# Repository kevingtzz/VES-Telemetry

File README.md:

## VES-Telemetry 🚀
Telemetry system for electro-solar vehicle VES-KRATOS
## Hardware 🔧
API frames reception and emission for Zigbee mesh topology architecture implemented on Xbee.
CAN protocol data extraction, processing and emission (Low level).
## Software ⚙️
Multi platform aplication on Electron JS for GPS geolocation and electro-solar vehicle data monitoring on real time.
## Initialization:
* Install dependencies with npm install.
* Install RethinkDB, if you have macOS with homebrew just type on your terminal "brew update && brew install rethinkdb".
* Create the database, go to localhost:8080 and create a database with this name "KRATOS-VES".

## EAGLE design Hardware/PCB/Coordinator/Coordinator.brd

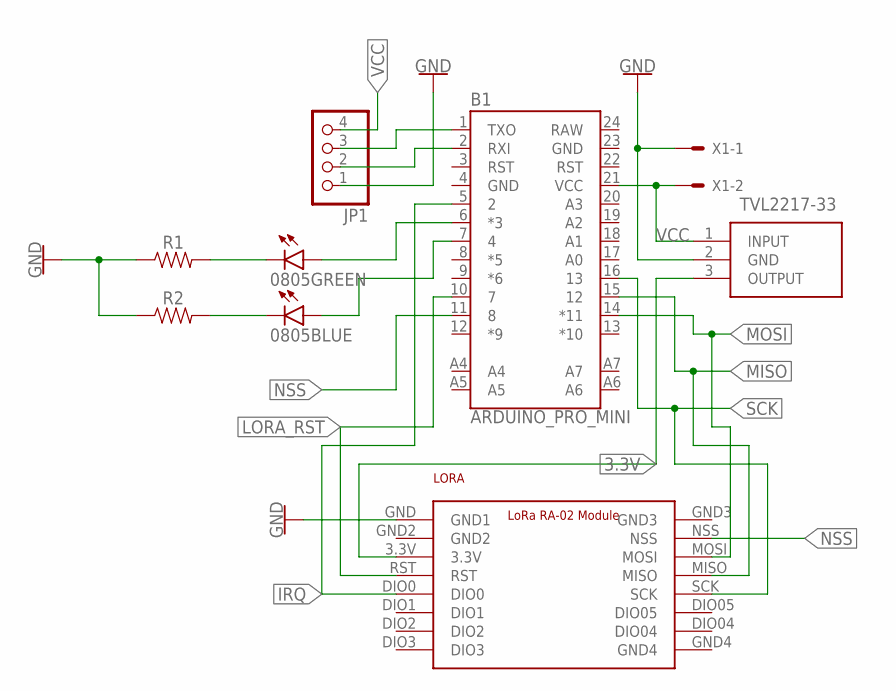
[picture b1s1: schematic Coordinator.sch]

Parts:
0805BLUE, 0805GREEN: LEDCHIPLED_0805; CHIPLED_0805
B1: ARDUINO_PRO_MINI
JP1: PINHD-1X4; 1X04
LORA: LORA_RA-02_MODULE; LORA_RA-02_MODULE_FOOTPRINT
R1, R2: 0805
TVL2217-33: TLV2217-33KCSE3; TO254P470X1016X1965-3P
X1: JST-XH-02-PIN-LONG-PAD; JST-XH-02-PACKAGE-LONG-PAD

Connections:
3.3V: LORA.3.3V, TVL2217-33.3 (OUTPUT)
GND: B1.4 (GND), B1.23 (GND), JP1.1, LORA.GND (GND1), R1.1, R2.1, TVL2217-33.2 (GND), X1.1
IRQ: B1.5 (2), LORA.DIO0
LORA_RST: B1.10 (7), LORA.RST
MISO: B1.15 (12), LORA.MISO
MOSI: B1.14 (*11), LORA.MOSI
unnamed: B1.2 (RXI), JP1.2
unnamed: B1.1 (TXO), JP1.3
unnamed: 0805GREEN.A, B1.6 (*3)
unnamed: 0805BLUE.A, B1.7 (4)
unnamed: 0805GREEN.C, R1.2
unnamed: 0805BLUE.C, R2.2
NSS: B1.11 (8), LORA.NSS
RAW: B1.24 (RAW)
SCK: B1.16 (13), LORA.SCK
VCC: B1.21 (VCC), JP1.4, TVL2217-33.1 (INPUT), X1.2

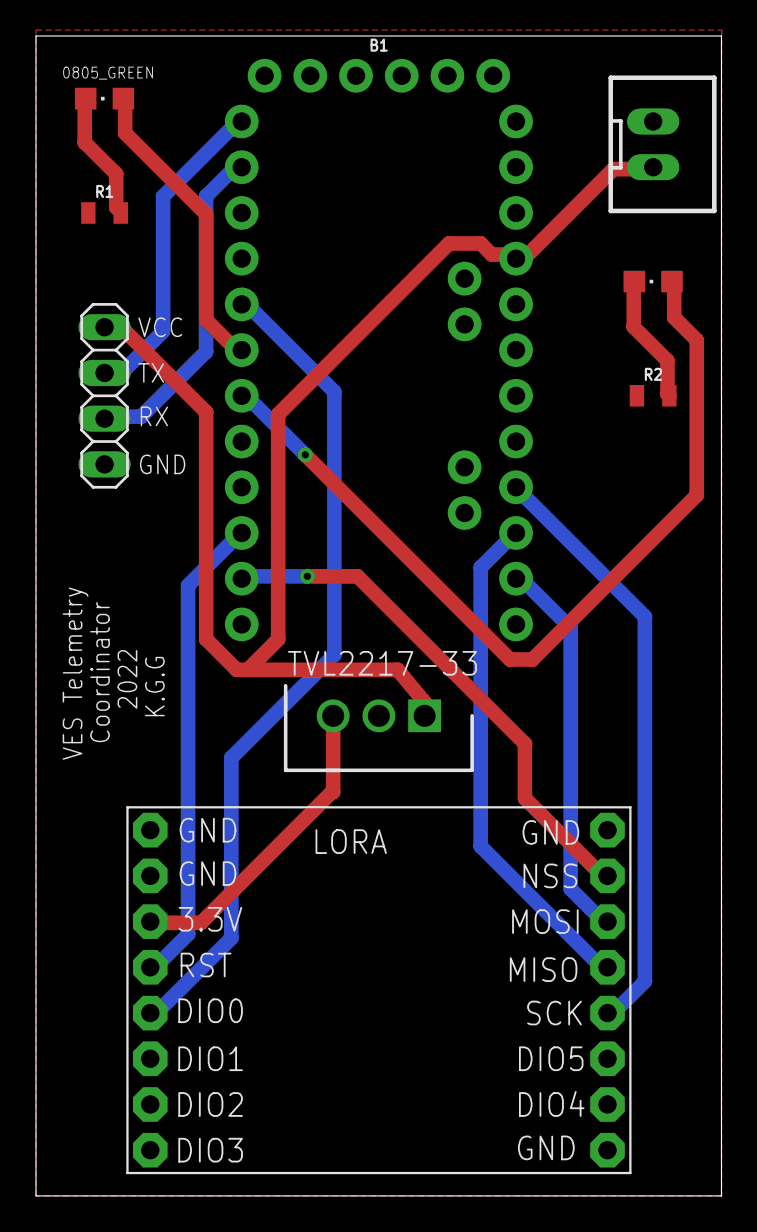
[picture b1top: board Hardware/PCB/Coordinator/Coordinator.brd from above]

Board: 2 copper layers, 38.1 x 64.4 mm, 9 parts (0 on the bottom side), 15 nets.

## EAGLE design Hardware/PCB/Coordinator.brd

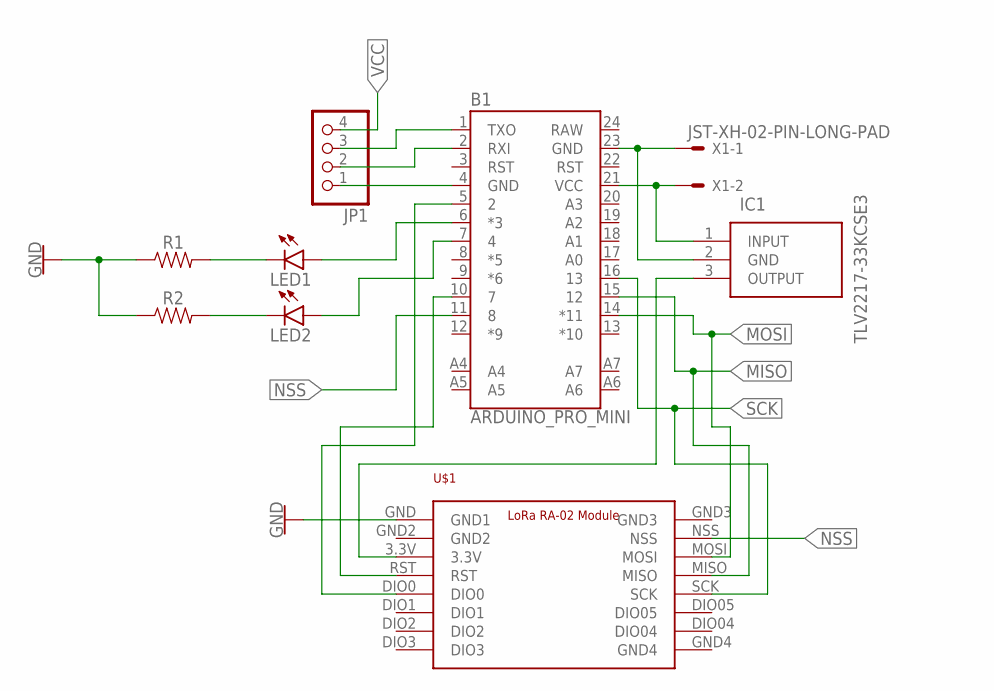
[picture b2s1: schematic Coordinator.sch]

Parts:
B1: ARDUINO_PRO_MINI
IC1: TLV2217-33KCSE3; TO254P470X1016X1965-3P
JP1: PINHD-1X4; 1X04
LED1, LED2: LEDCHIPLED_0805; CHIPLED_0805
R1, R2: 0805
U$1: LORA_RA-02_MODULE; LORA_RA-02_MODULE_FOOTPRINT
X1: JST-XH-02-PIN-LONG-PAD; JST-XH-02-PACKAGE-LONG-PAD

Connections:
GND: R1.1, R2.1, U$1.GND (GND1)
MISO: B1.15 (12), U$1.MISO
MOSI: B1.14 (*11), U$1.MOSI
unnamed: B1.23 (GND), IC1.2 (GND), X1.1
unnamed: B1.21 (VCC), IC1.1 (INPUT), X1.2
unnamed: IC1.3 (OUTPUT), U$1.3.3V
unnamed: B1.4 (GND), JP1.1
unnamed: B1.2 (RXI), JP1.2
unnamed: B1.1 (TXO), JP1.3
unnamed: B1.5 (2), U$1.DIO0
unnamed: B1.10 (7), U$1.RST
unnamed: B1.6 (*3), LED1.A
unnamed: B1.7 (4), LED2.A
unnamed: LED1.C, R1.2
unnamed: LED2.C, R2.2
NSS: B1.11 (8), U$1.NSS
RAW: B1.24 (RAW)
SCK: B1.16 (13), U$1.SCK
VCC: JP1.4

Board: 2 copper layers, 9 parts (0 on the bottom side), 17 nets, no tracks yet.

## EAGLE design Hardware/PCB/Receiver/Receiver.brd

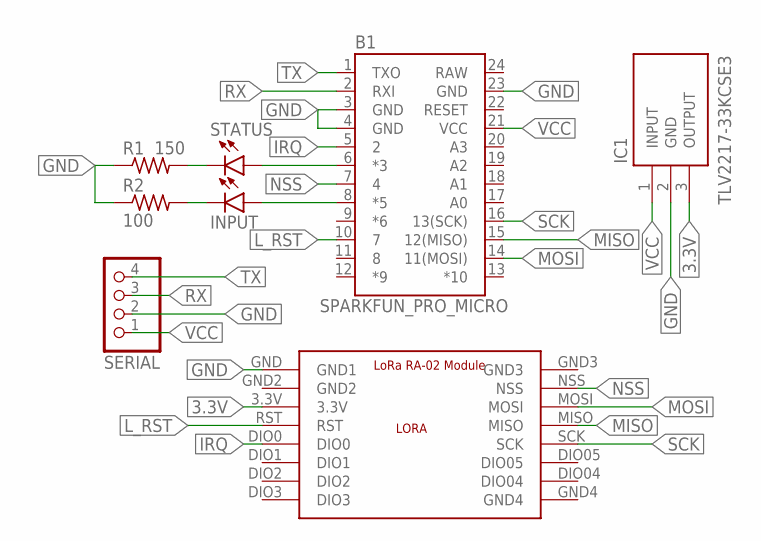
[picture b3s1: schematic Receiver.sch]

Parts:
B1: SPARKFUN_PRO_MICRO
IC1: TLV2217-33KCSE3; TO254P470X1016X1965-3P
INPUT: LEDSML0805; SML0805
LORA: LORA_RA-02_MODULE; LORA_RA-02_MODULE_FOOTPRINT
R1: 150; R0805
R2: 100; R0805
SERIAL: PINHD-1X4; 1X04
STATUS: LEDSML0805; SML0805

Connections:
3.3V: IC1.3 (OUTPUT), LORA.3.3V
GND: B1.3 (GND), B1.4 (GND), B1.23 (GND), IC1.2 (GND), LORA.GND (GND1), R1.1, R2.1, SERIAL.2
IRQ: B1.5 (2), LORA.DIO0
L_RST: B1.10 (7), LORA.RST
MISO: B1.15 (12(MISO)), LORA.MISO
MOSI: B1.14 (11(MOSI)), LORA.MOSI
unnamed: B1.6 (*3), STATUS.A
unnamed: B1.8 (*5), INPUT.A
unnamed: INPUT.C, R2.2
NSS: B1.7 (4), LORA.NSS
RAW: B1.24 (RAW)
RX: B1.2 (RXI), SERIAL.3
SCK: B1.16 (13(SCK)), LORA.SCK
STATUS: R1.2, STATUS.C
TX: B1.1 (TXO), SERIAL.4
VCC: B1.21 (VCC), IC1.1 (INPUT), SERIAL.1

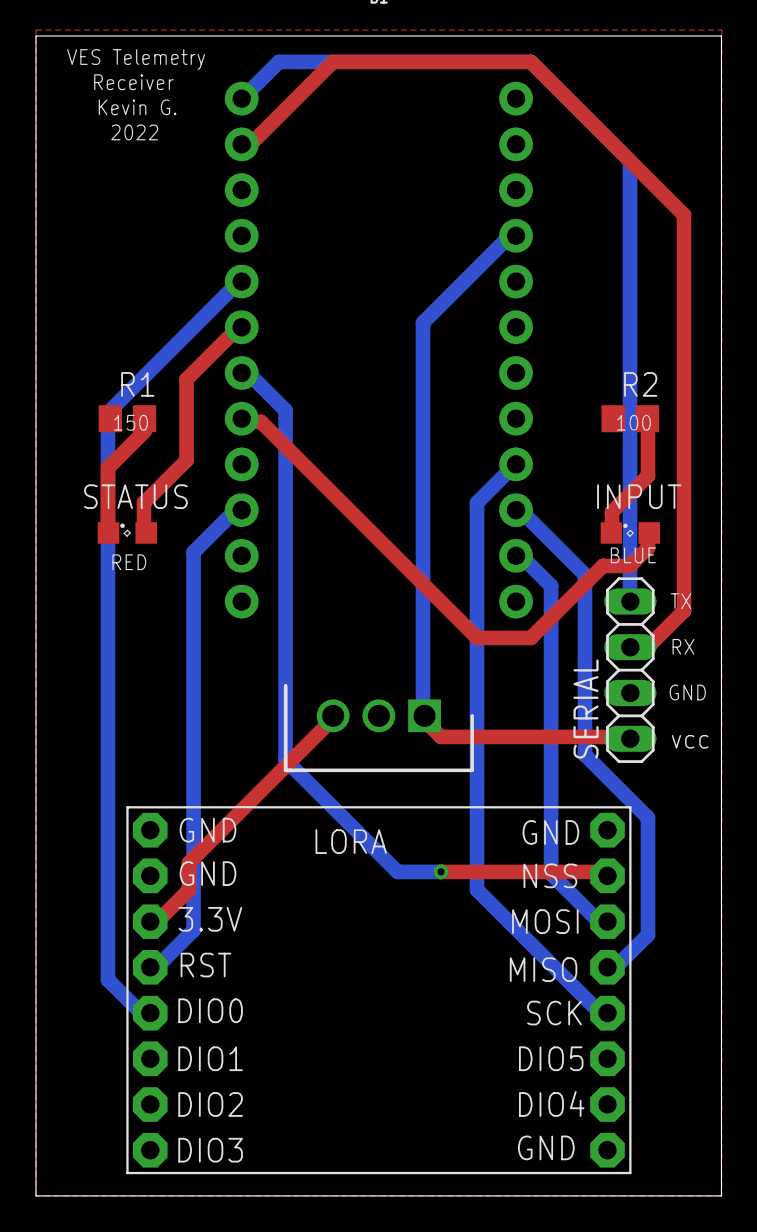
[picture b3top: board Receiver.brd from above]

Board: 2 copper layers, 38.1 x 64.4 mm, 8 parts (0 on the bottom side), 15 nets.

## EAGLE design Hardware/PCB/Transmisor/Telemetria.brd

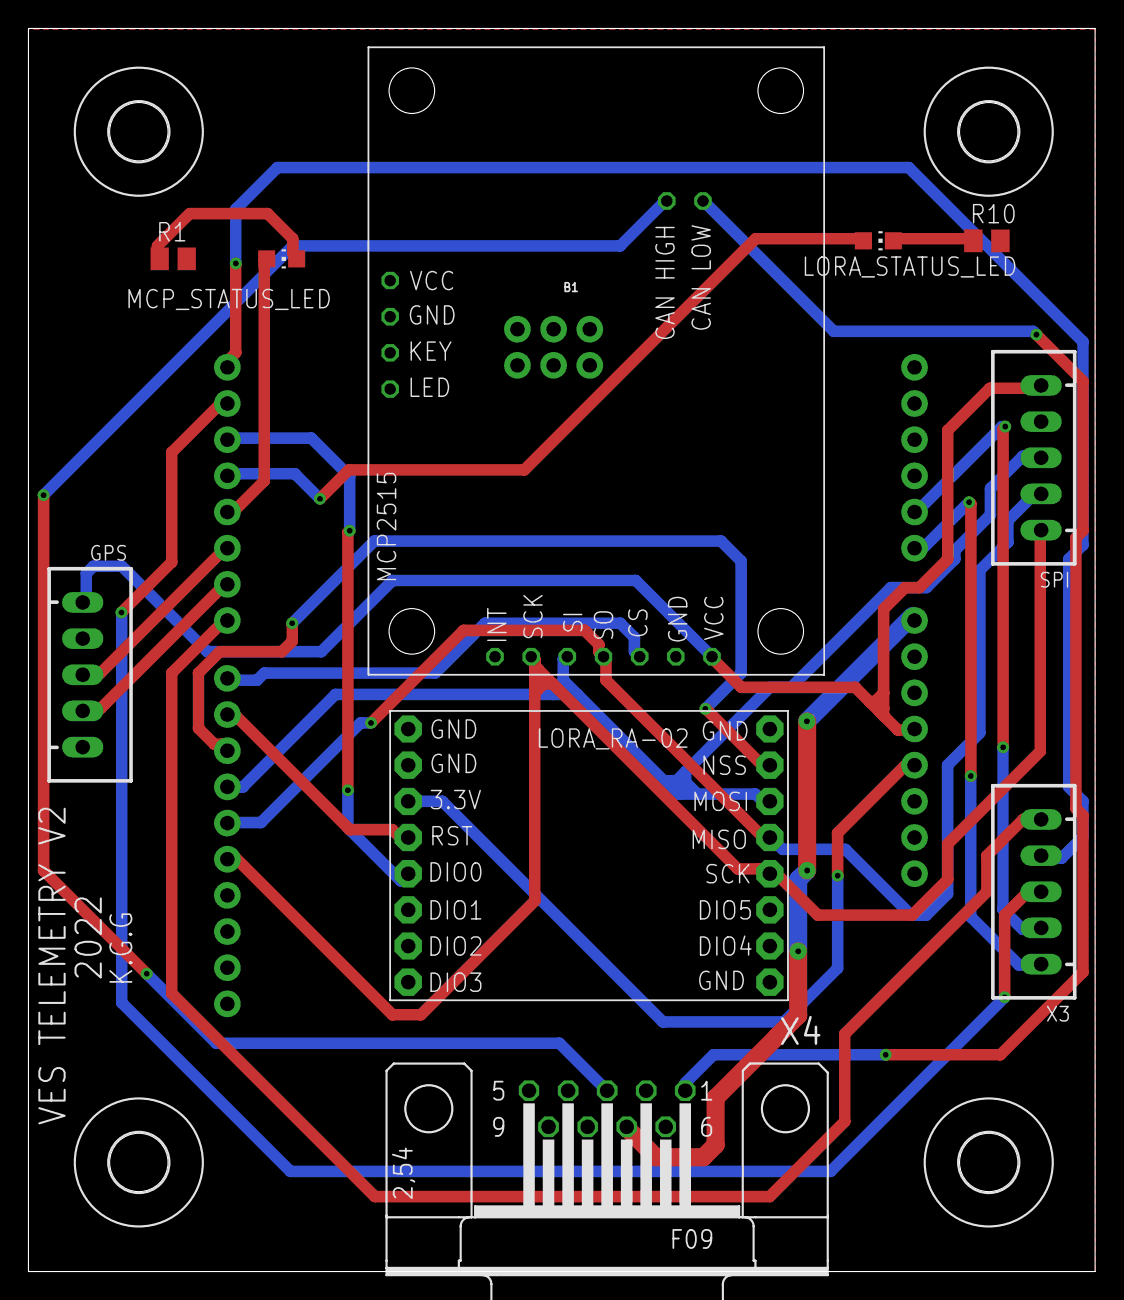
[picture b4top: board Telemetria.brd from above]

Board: 2 copper layers, 74.9 x 87.3 mm, 15 parts (0 on the bottom side), 24 nets.

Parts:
B1: ARDUINO_UNO_R3_SHIELD_ICSP-NO_LABELS; UNO_R3_SHIELD_ICSP_NOLABELS
GPS: JST-XH-05-PIN-LONG-PAD; JST-XH-05-PACKAGE-LONG-PAD
LORA_RA-02: LORA_RA-02_MODULE; LORA_RA-02_MODULE_FOOTPRINT
LORA_STATUS_LED: CHIP-LED0805
MCP2515: MCP2515
MCP_STATUS_LED: CHIP-LED0805
R1, R10: M0805
SPI: JST-XH-05-PIN-LONG-PAD; JST-XH-05-PACKAGE-LONG-PAD
U$1, U$2, U$3, U$4: 4,1
X3: JST-XH-05-PIN-LONG-PAD; JST-XH-05-PACKAGE-LONG-PAD
X4: F09H

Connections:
3.3V: B1.3.3V, LORA_RA-02.3.3V
+5V: B1.5V, GPS.1, MCP2515.VCC, SPI.5
A0: B1.A0, X3.1
A1: B1.A1, X3.2
CAN_H: MCP2515.CAN_HIGH, X4.3
CAN_L: MCP2515.CAN_LOW, X4.1
D7: B1.D7, X3.5
GND: B1.GND@2, GPS.2, LORA_RA-02.GND, MCP2515.GND, R1.2, R10.2, SPI.4, X4.5
LORA_IRQ: B1.D2, LORA_RA-02.DIO0
LORA_LED: B1.D3, LORA_STATUS_LED.A
LORA_NSS: B1.D10, LORA_RA-02.NSS
LORA_RST: B1.D9, LORA_RA-02.RST
MCP_CS: B1.D8, MCP2515.CS
MCP_LED: B1.D4, MCP_STATUS_LED.A
MISO: B1.D12, LORA_RA-02.MISO, MCP2515.SO, SPI.2
MOSI: B1.D11, LORA_RA-02.MOSI, MCP2515.SI, SPI.3
unnamed: LORA_STATUS_LED.C, R10.1
unnamed: MCP_STATUS_LED.C, R1.1
RX: B1.RX, X3.4
SCK: B1.D13, LORA_RA-02.SCK, MCP2515.SCK, SPI.1
SRX: B1.D5, GPS.3
STX: B1.D6, GPS.4
TX: B1.TX, X3.3
VIN_12V: B1.VIN, X4.7

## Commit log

2021-11-02 VES-Telemetry 1.0 added
2021-11-02 Firs commit
2021-11-02 gitignore updated
2021-11-28 feat(serial): Json serial input imput implemented
2021-12-12 feat(Hardware, software): first test raw data done
2022-02-23 feat(database): database window added
2022-02-23 fix(tables): table generator fixed
2022-02-26 fix(get and delete): database almost done.
2022-04-06 feat(Serial): serail comunications and gps done
2022-04-07 feat(database): database indicators and pushing data done
2022-04-07 feat(graph): graphics operative, styles left
2022-06-12 feat(Transmissor): PCB Transmissor finished
2022-06-12 fix(transmissor): transmisson pcb updated
2022-06-16 receiver case v1
2022-07-06 feat(protocol&PCB): RadioHead router protocol done, receiver pcb done
2022-11-09 commit after race

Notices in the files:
parts and their libraries:
SparkFun-Boards: Licensing: Creative Commons ShareAlike 4.0 International - https://creativecommons.org/licenses/by-sa/4.0
